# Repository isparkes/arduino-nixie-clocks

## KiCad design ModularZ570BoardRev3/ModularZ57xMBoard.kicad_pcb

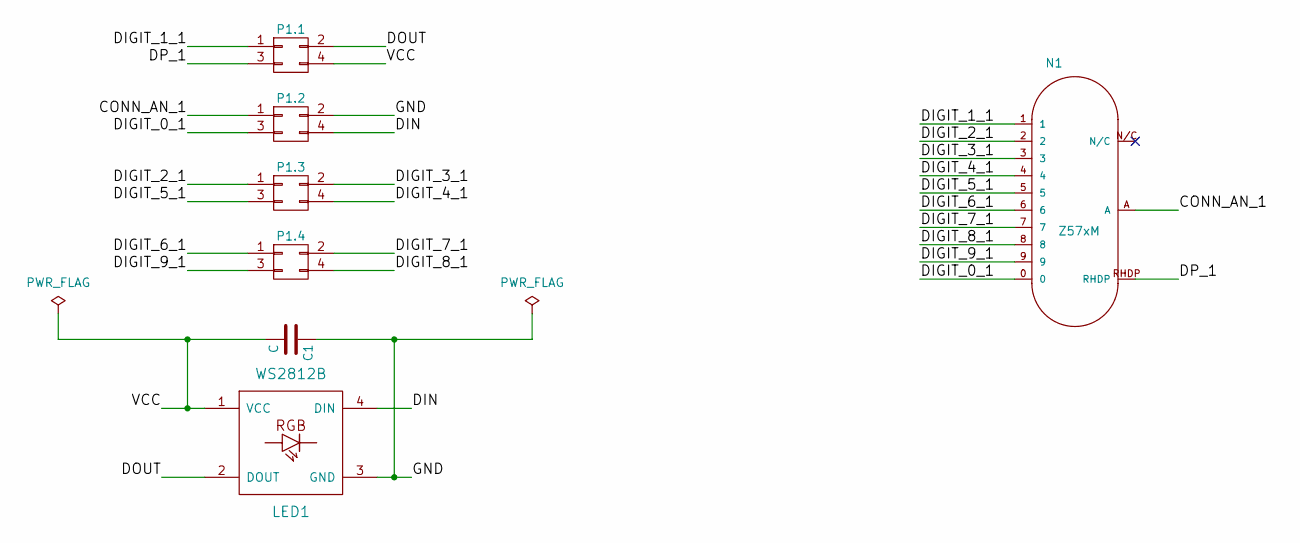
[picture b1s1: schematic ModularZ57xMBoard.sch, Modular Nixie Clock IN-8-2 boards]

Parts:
C1: C; C_1206_HandSoldering
LED1: WS2812B
N1: Z57xM; Z570M
P1.1, P1.2, P1.3, P1.4: CONN_02X02; Header_MA02-2

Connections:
/CONN_AN_1: N1.A, P1.2.1
/DIGIT_0_1: N1.0, P1.2.3
/DIGIT_1_1: N1.1, P1.1.1
/DIGIT_2_1: N1.2, P1.3.1
/DIGIT_3_1: N1.3, P1.3.2
/DIGIT_4_1: N1.4, P1.3.4
/DIGIT_5_1: N1.5, P1.3.3
/DIGIT_6_1: N1.6, P1.4.1
/DIGIT_7_1: N1.7, P1.4.2
/DIGIT_8_1: N1.8, P1.4.4
/DIGIT_9_1: N1.9, P1.4.3
/DIN: LED1.4 (DIN), P1.2.4
/DOUT: LED1.2 (DOUT), P1.1.2
/DP_1: N1.RHDP, P1.1.3
/GND: C1.1, LED1.3 (GND), P1.2.2
/VCC: C1.2, LED1.1 (VCC), P1.1.4

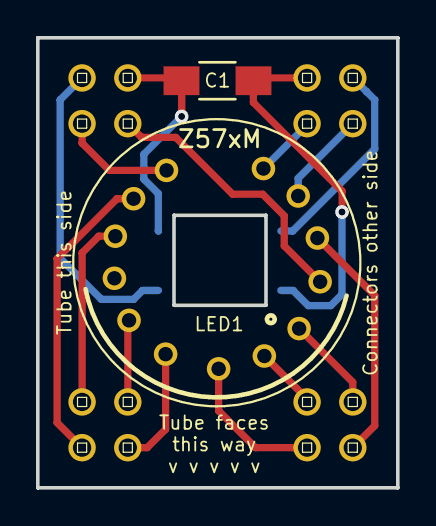
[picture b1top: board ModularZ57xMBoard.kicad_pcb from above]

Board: 2 copper layers, 20.0 x 25.0 mm, 7 parts (0 on the bottom side), 16 nets.

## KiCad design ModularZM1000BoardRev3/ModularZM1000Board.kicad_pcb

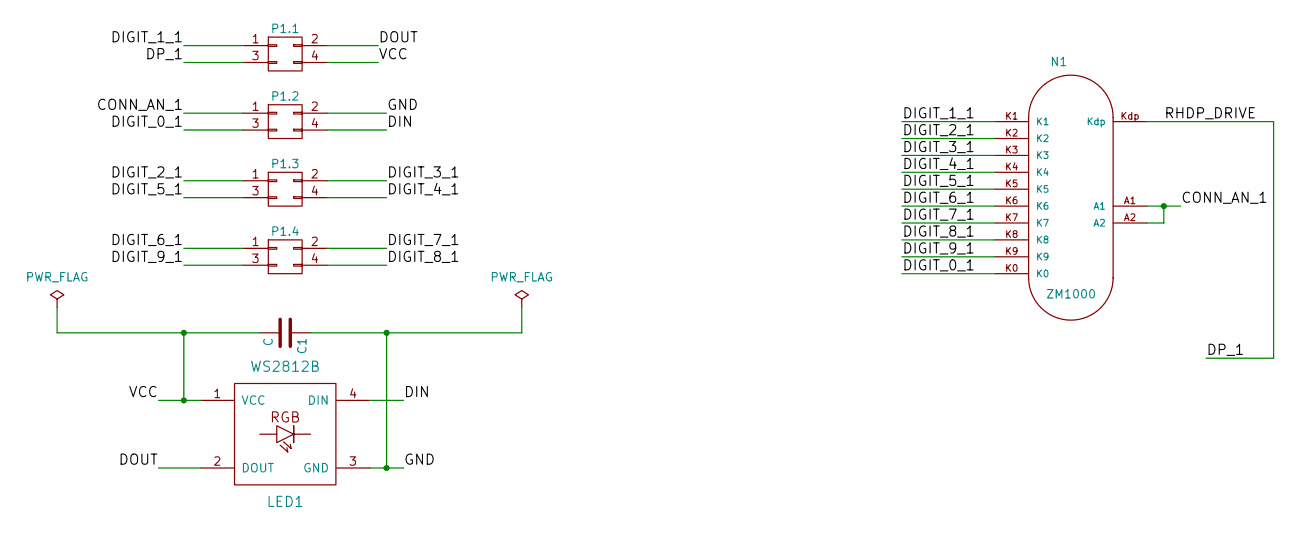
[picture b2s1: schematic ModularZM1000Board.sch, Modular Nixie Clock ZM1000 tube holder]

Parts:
C1: C; C_1206_HandSoldering
LED1: WS2812B
N1: ZM1000
P1.1, P1.2, P1.3, P1.4: CONN_02X02; Header_MA02-2

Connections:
/CONN_AN_1: N1.A1, N1.A2, P1.2.1
/DIGIT_0_1: N1.K0, P1.2.3
/DIGIT_1_1: N1.K1, P1.1.1
/DIGIT_2_1: N1.K2, P1.3.1
/DIGIT_3_1: N1.K3, P1.3.2
/DIGIT_4_1: N1.K4, P1.3.4
/DIGIT_5_1: N1.K5, P1.3.3
/DIGIT_6_1: N1.K6, P1.4.1
/DIGIT_7_1: N1.K7, P1.4.2
/DIGIT_8_1: N1.K8, P1.4.4
/DIGIT_9_1: N1.K9, P1.4.3
/DIN: LED1.4 (DIN), P1.2.4
/DOUT: LED1.2 (DOUT), P1.1.2
/DP_1: N1.Kdp, P1.1.3
/GND: C1.1, LED1.3 (GND), P1.2.2
/VCC: C1.2, LED1.1 (VCC), P1.1.4

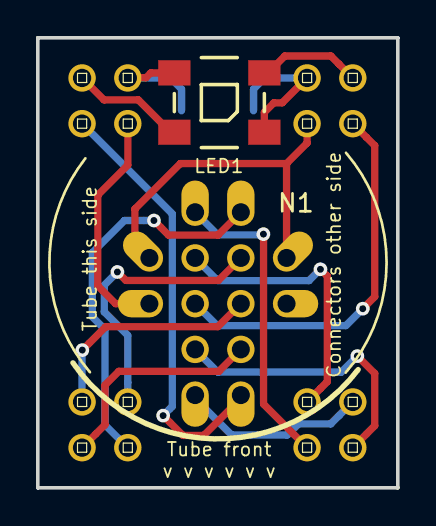
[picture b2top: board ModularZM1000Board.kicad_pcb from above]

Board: 2 copper layers, 20.0 x 25.0 mm, 7 parts (1 on the bottom side), 16 nets.

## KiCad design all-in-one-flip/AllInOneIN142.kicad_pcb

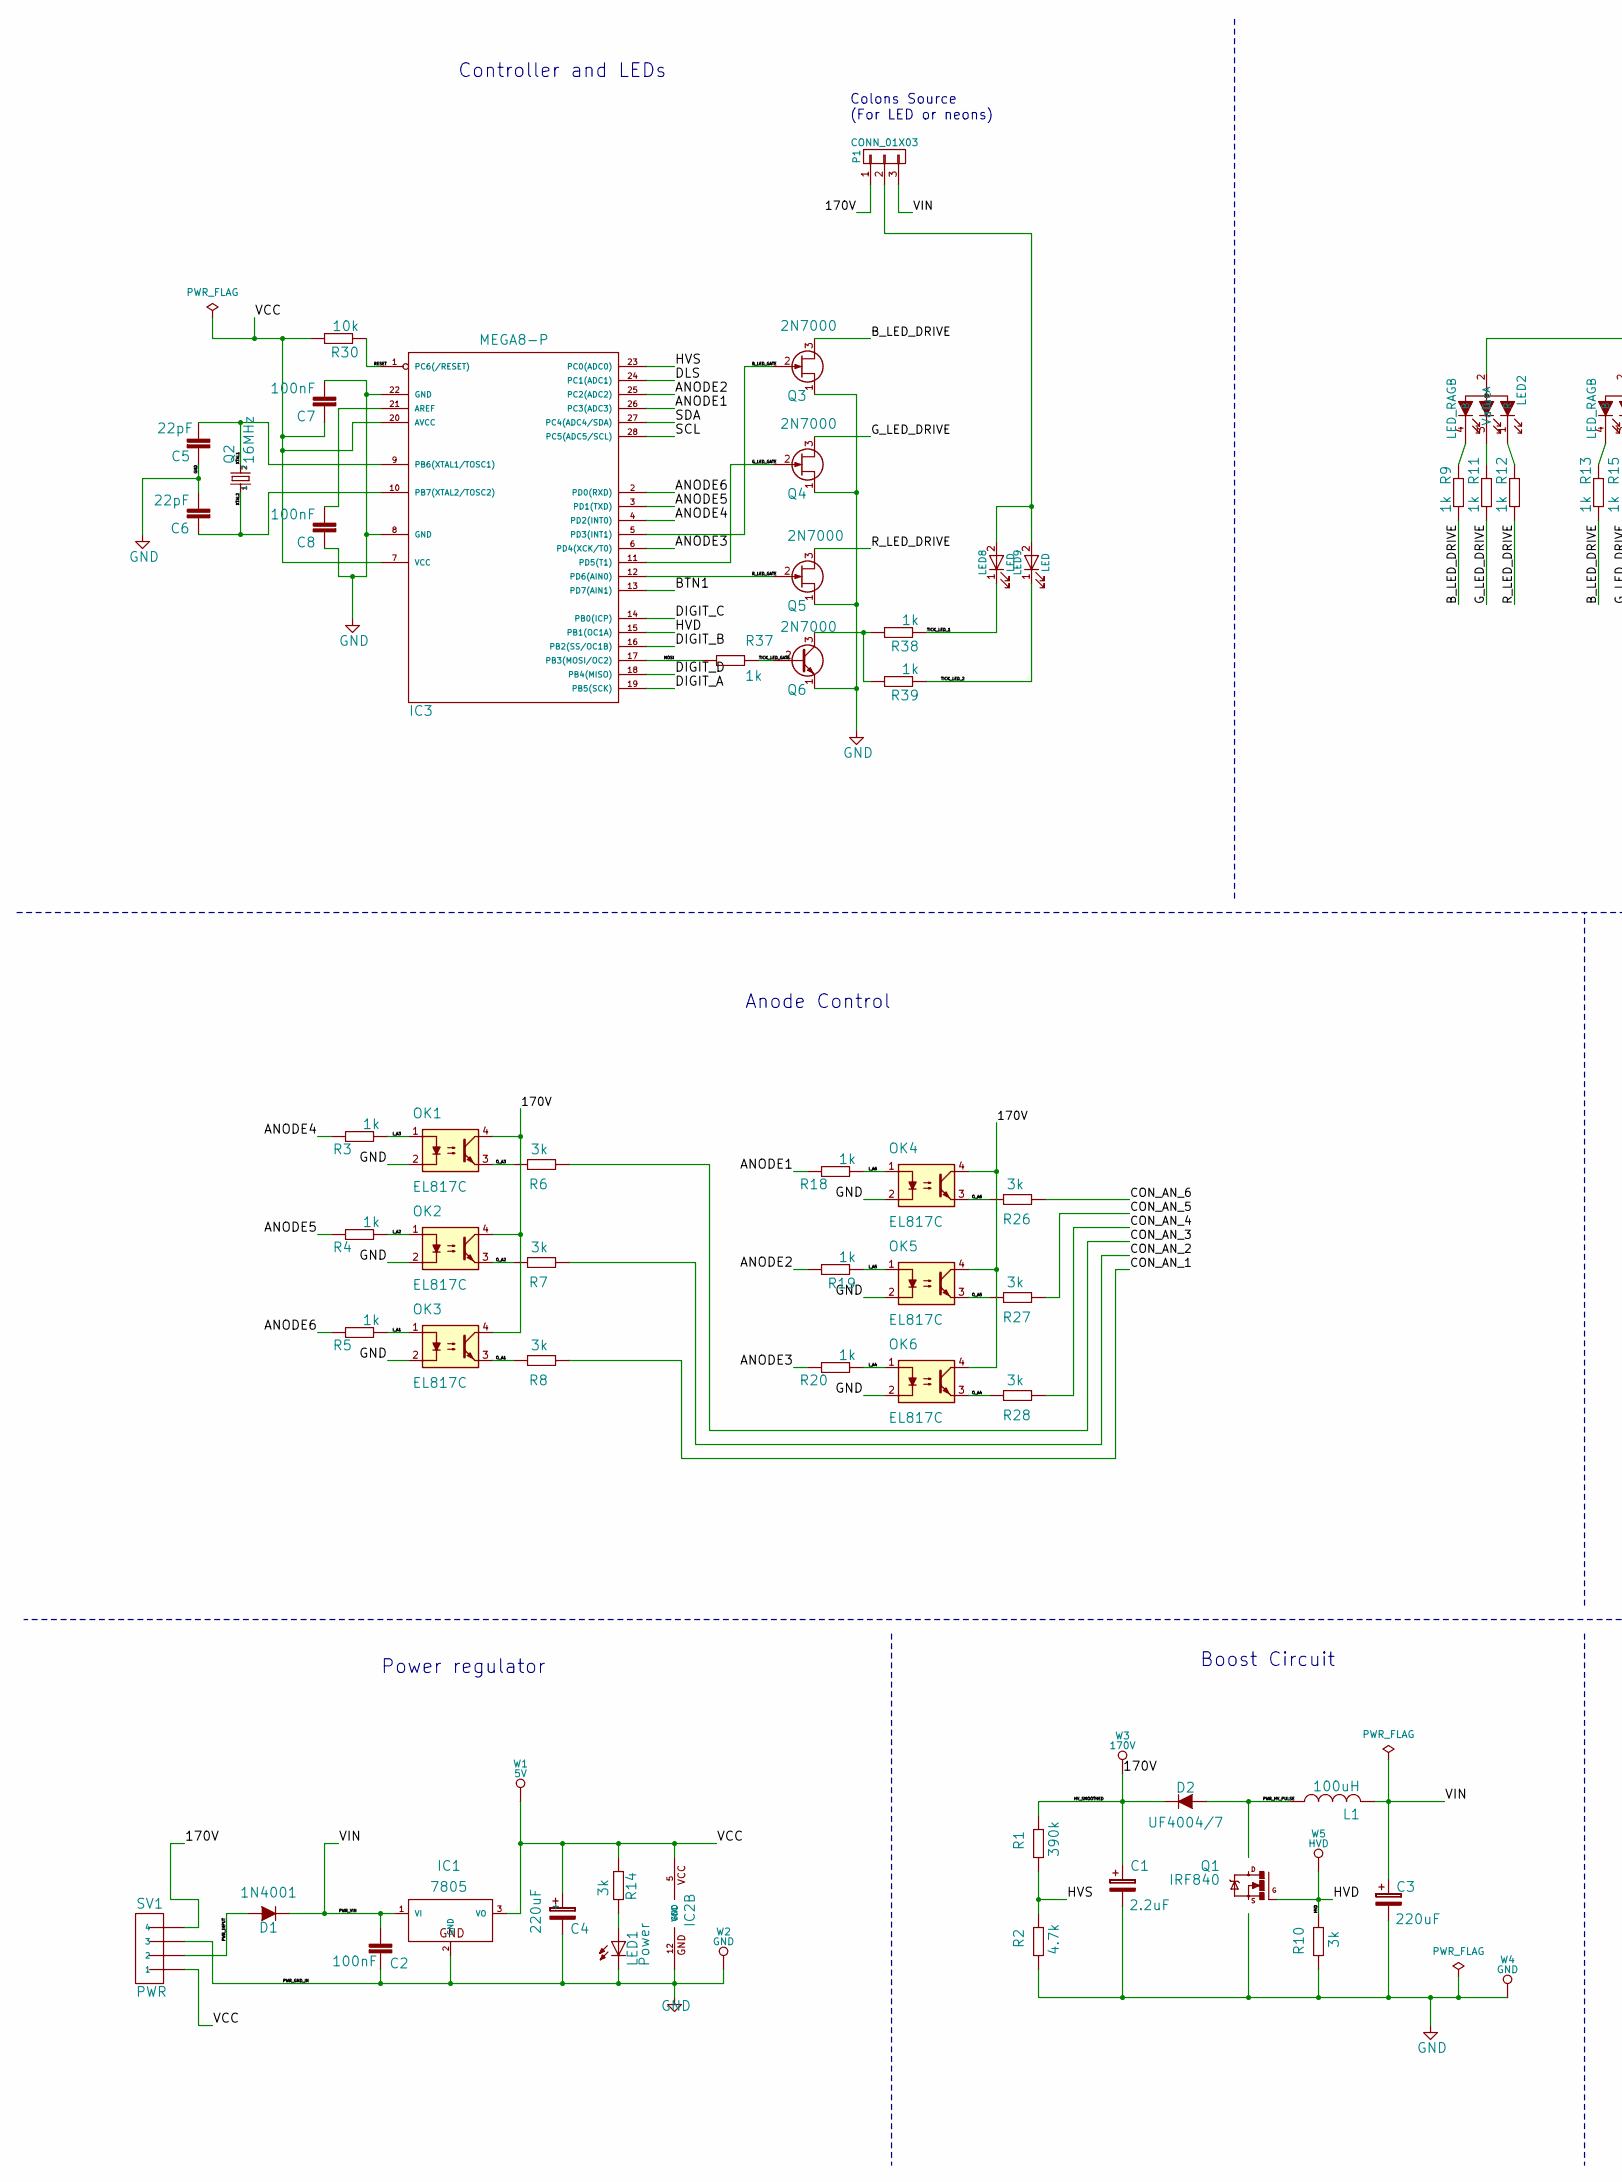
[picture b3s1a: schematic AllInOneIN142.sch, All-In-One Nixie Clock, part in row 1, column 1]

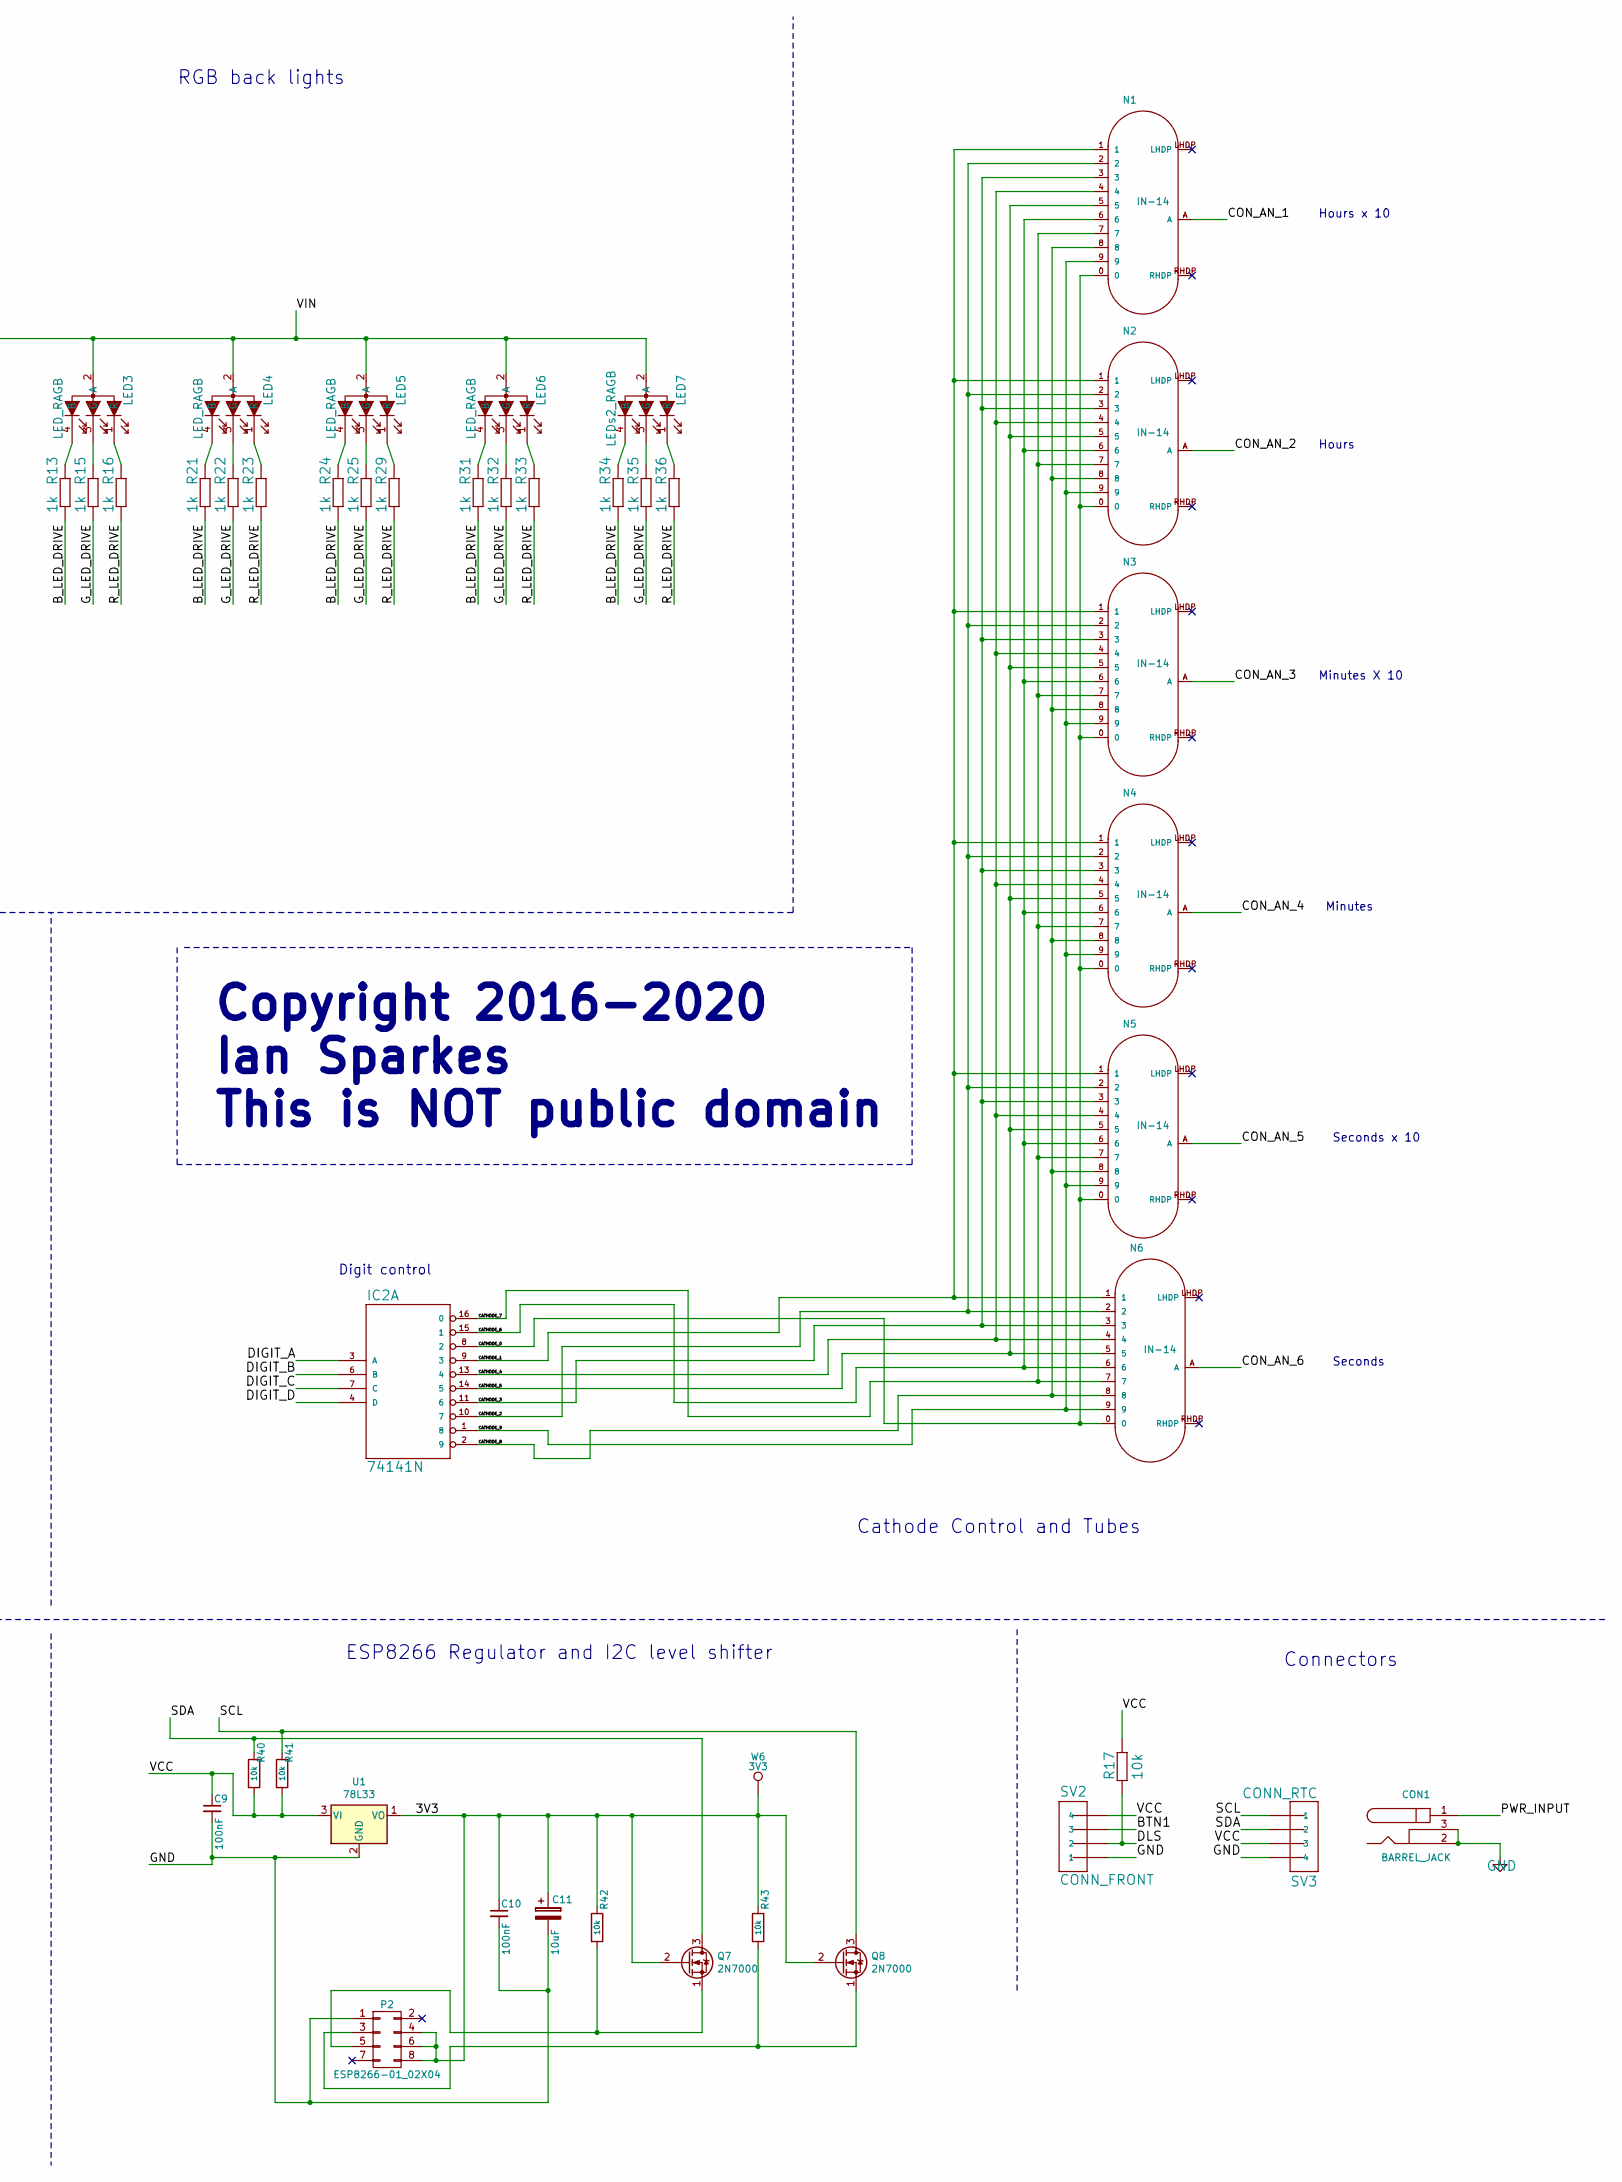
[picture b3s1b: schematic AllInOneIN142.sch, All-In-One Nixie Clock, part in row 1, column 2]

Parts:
C1: 2.2uF; C_Radial_D10_L11.2_P2.5_3.5
C2, C7, C8, C9, C10: 100nF; C025-024X044
C3, C4: 220uF; C_Radial_D6.3_L11.2_P2.5
C5, C6: 22pF; C025-024X044
C11: 10uF; C_Radial_D6.3_L11.2_P2.5
CON1: BARREL_JACK
D1: 1N4001; Diode_DO-41_1N4001
D2: UF4004/7; Diode_DO-41_1N4001
IC1: 7805; TRANSISTOR-POWER_TO220BV
IC2: 74141N; 74141_DIL16
IC3: MEGA8-P; 328P_DIL28
L1: 100uH; Inductor-100mH
LED1: Power; LED_3MM
LED2, LED3, LED4, LED5, LED6: LED_RAGB; LED5_RGB_CA_Offset
LED7: LEDs2_RAGB; LED5_RGB_CA_Offset
LED8, LED9: LED; LED-5MM-Centred
N1, N2, N3, N4, N5, N6: IN-14
OK1, OK2, OK3, OK4, OK5, OK6: EL817C; optocoupler-DIL04
P1: CONN_01X03; Header_MA03-1
P2: ESP8266-01_02X04; ESP8266_2x04
Q1: IRF840; 2N7000_TO92
Q2: 16MHz; Crystal_HC49-U_Vertical
Q3, Q4, Q5: 2N7000; TO-92_inline_2N7000
Q6: 2N7000; TO-92_inline_MPSA42
Q7, Q8: 2N7000; TO-92_2N7000_inline
R1: 390k; R-0207_2V
R2: 4.7k; R-0207_2V
R3, R4, R5, R9, R11, R12, R13, R15, R16, R18, R19, R20, R21, R22, R23, R24, R25, R29, R31, R32, R33, R34, R35, R36, R37, R38, R39: 1k; R-0207_2V
R6, R7, R8, R10, R14, R26, R27, R28: 3k; R-0207_2V
R17, R30, R40, R41, R42, R43: 10k; R-0207_2V
SV1: PWR; Header_MA04-1
SV2: CONN_FRONT; Header_MA04-1
SV3: CONN_RTC; Header_MA04-1
U1: 78L33; TO-92_2N7000_inline
W1: 5V; TESTPAD_P1-13
W2, W4: GND; TESTPAD_P1-13
W3: 170V; TESTPAD_P1-13
W5: HVD; TESTPAD_P1-13
W6: 3V3; TESTPAD_P1-13

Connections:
/3V3: C10.1, C11.1, P2.4 (CH_EN), P2.6 (RST), P2.8 (VCC), Q7.2 (G), Q8.2 (G), R42.1, R43.1, U1.1 (VO), W6.1
/170V: C1.1, D2.1 (K), OK1.4, OK2.4, OK3.4, OK4.4, OK5.4, OK6.4, P1.1, R1.2, SV1.4, W3.1
/ANODE1: IC3.26 (PC3(ADC3)), R18.2
/ANODE2: IC3.25 (PC2(ADC2)), R19.2
/ANODE3: IC3.6 (PD4(XCK/T0)), R20.2
/ANODE4: IC3.4 (PD2(INT0)), R3.2
/ANODE5: IC3.3 (PD1(TXD)), R4.2
/ANODE6: IC3.2 (PD0(RXD)), R5.2
/BTN1: IC3.13 (PD7(AIN1)), SV2.3
/B_LED_DRIVE: Q3.3 (D), R9.1, R13.1, R21.1, R24.1, R31.1, R34.1
/B_LED_GATE: IC3.5 (PD3(INT1)), Q3.2 (G)
/CATHODE_0: IC2.8 (2), N1.0, N2.0, N3.0, N4.0, N5.0, N6.0
/CATHODE_1: IC2.9 (3), N1.1, N2.1, N3.1, N4.1, N5.1, N6.1
/CATHODE_2: IC2.10 (7), N1.2, N2.2, N3.2, N4.2, N5.2, N6.2
/CATHODE_3: IC2.11 (6), N1.3, N2.3, N3.3, N4.3, N5.3, N6.3
/CATHODE_4: IC2.13 (4), N1.4, N2.4, N3.4, N4.4, N5.4, N6.4
/CATHODE_5: IC2.14 (5), N1.5, N2.5, N3.5, N4.5, N5.5, N6.5
/CATHODE_6: IC2.15 (1), N1.6, N2.6, N3.6, N4.6, N5.6, N6.6
/CATHODE_7: IC2.16 (0), N1.7, N2.7, N3.7, N4.7, N5.7, N6.7
/CATHODE_8: IC2.2 (9), N1.8, N2.8, N3.8, N4.8, N5.8, N6.8
/CATHODE_9: IC2.1 (8), N1.9, N2.9, N3.9, N4.9, N5.9, N6.9
/CON_AN_1: N1.A, R8.1
/CON_AN_2: N2.A, R7.1
/CON_AN_3: N3.A, R6.1
/CON_AN_4: N4.A, R28.1
/CON_AN_5: N5.A, R27.1
/CON_AN_6: N6.A, R26.1
/DIGIT_A: IC2.3 (A), IC3.19 (PB5(SCK))
/DIGIT_B: IC2.6 (B), IC3.16 (PB2(SS/OC1B))
/DIGIT_C: IC2.7 (C), IC3.14 (PB0(ICP))
/DIGIT_D: IC2.4 (D), IC3.18 (PB4(MISO))
/DLS: IC3.24 (PC1(ADC1)), R17.1, SV2.2
/G_LED_DRIVE: Q4.3 (D), R11.1, R15.1, R22.1, R25.1, R32.1, R35.1
/G_LED_GATE: IC3.11 (PD5(T1)), Q4.2 (G)
/HVD: IC3.15 (PB1(OC1A)), Q1.1, Q1.G, R10.2, W5.1
/HVS: IC3.23 (PC0(ADC0)), R1.1, R2.2
/I_A1: OK3.1, R5.1
/I_A2: OK2.1, R4.1
/I_A3: OK1.1, R3.1
/I_A4: OK6.1, R20.1
/I_A5: OK5.1, R19.1
/I_A6: OK4.1, R18.1
/MOSI: IC3.17 (PB3(MOSI/OC2)), R37.1
/O_A1: OK3.3, R8.2
/O_A2: OK2.3, R7.2
/O_A3: OK1.3, R6.2
/O_A4: OK6.3, R28.2
/O_A5: OK5.3, R27.2
/O_A6: OK4.3, R26.2
/PWR_HV_PULSE: D2.2 (A), L1.1, Q1.2, Q1.D
/PWR_INPUT: CON1.1, D1.2 (A), SV1.2
/PWR_VIN: C2.2, C3.1, D1.1 (K), IC1.1 (VI), L1.2, LED2.2 (A), LED3.2 (A), LED4.2 (A), LED5.2 (A), LED6.2 (A), LED7.2 (A), P1.3
/RESET: IC3.1 (PC6(/RESET)), R30.1
/R_LED_DRIVE: Q5.3 (D), R12.1, R16.1, R23.1, R29.1, R33.1, R36.1
/R_LED_GATE: IC3.12 (PD6(AIN0)), Q5.2 (G)
/SCL: IC3.28 (PC5(ADC5/SCL)), Q8.3 (D), R41.1, SV3.1
/SDA: IC3.27 (PC4(ADC4/SDA)), Q7.3 (D), R40.1, SV3.2
/TICK_LED_1: LED8.1 (K), R38.1
/TICK_LED_2: LED9.1 (K), R39.1
/TICK_LED_GATE: Q6.2 (B), R37.2
/VCC: C4.1, C7.1, C9.1, IC1.3 (VO), IC2.5 (VCC), IC3.7 (VCC), IC3.20 (AVCC), R14.1, R17.2, R30.2, R40.2, R41.2, SV1.1, SV2.4, SV3.3, U1.3 (VI), W1.1
/XTAL1: C5.2, IC3.9 (PB6(XTAL1/TOSC1)), Q2.2
/XTAL2: C6.1, IC3.10 (PB7(XTAL2/TOSC2)), Q2.1
GND: C1.2, C2.1, C3.2, C4.2, C5.1, C6.2, C7.2, C8.1, C9.2, C10.2, C11.2, CON1.2, CON1.3, IC1.2 (GND), IC2.12 (GND), IC3.8 (GND), IC3.22 (GND), LED1.K (C), OK1.2, OK2.2, OK3.2, OK4.2, OK5.2, OK6.2, P2.1 (GND), Q1.3, Q1.S, Q3.1 (S), Q4.1 (S), Q5.1 (S), Q6.1 (E), R2.1, R10.1, SV1.3, SV2.1, SV3.4, U1.2 (GND), W2.1, W4.1; also elsewhere on the board
unnamed: C8.2, IC3.21 (AREF)
unnamed: LED1.A, R14.2
unnamed: LED2.1 (R), R12.2
unnamed: LED2.3 (G), R11.2
unnamed: LED2.4 (B), R9.2
unnamed: LED3.1 (R), R16.2
unnamed: LED3.3 (G), R15.2
unnamed: LED3.4 (B), R13.2
unnamed: LED4.1 (R), R23.2
unnamed: LED4.3 (G), R22.2
unnamed: LED4.4 (B), R21.2
unnamed: LED5.1 (R), R29.2
unnamed: LED5.3 (G), R25.2
unnamed: LED5.4 (B), R24.2
unnamed: LED6.1 (R), R33.2
unnamed: LED6.3 (G), R32.2
unnamed: LED6.4 (B), R31.2
unnamed: LED7.1 (R), R36.2
unnamed: LED7.3 (G), R35.2
unnamed: LED7.4 (B), R34.2
unnamed: LED8.2 (A), LED9.2 (A), P1.2
unnamed: P2.3 (GPIO2), Q8.1 (S), R43.2
unnamed: P2.5 (GPIO0), Q7.1 (S), R42.2
unnamed: Q6.3 (C), R38.2, R39.2

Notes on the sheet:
Boost Circuit
Anode Control
Power regulator
Digit control
Connectors
Seconds
Seconds x 10
Minutes
Minutes X 10
Hours
Hours x 10
Colons Source (For LED or neons)
ESP8266 Regulator and I2C level shifter
Copyright 2016-2020 Ian Sparkes This is NOT public domain
Cathode Control and Tubes
RGB back lights
Controller and LEDs

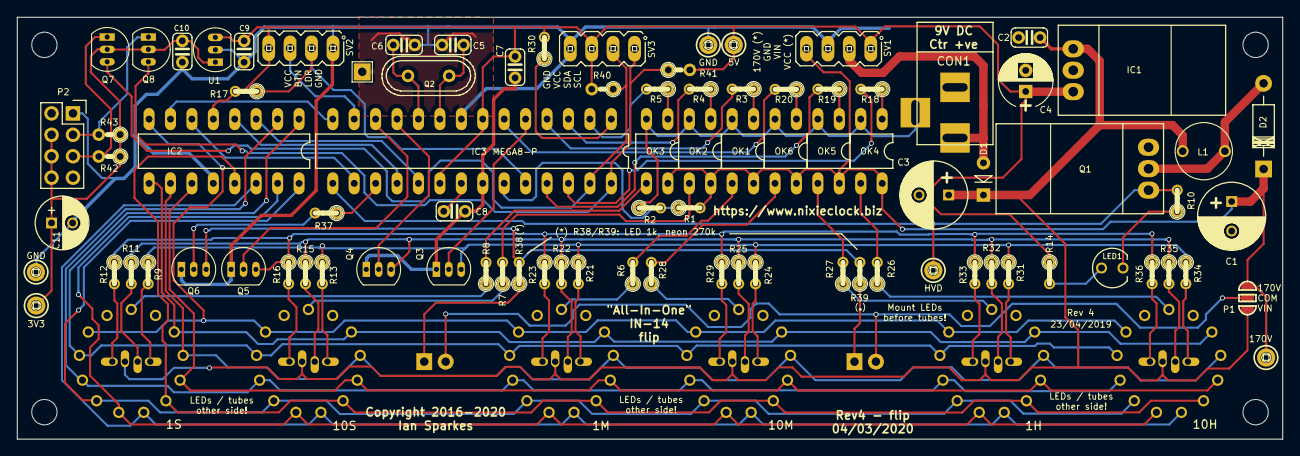
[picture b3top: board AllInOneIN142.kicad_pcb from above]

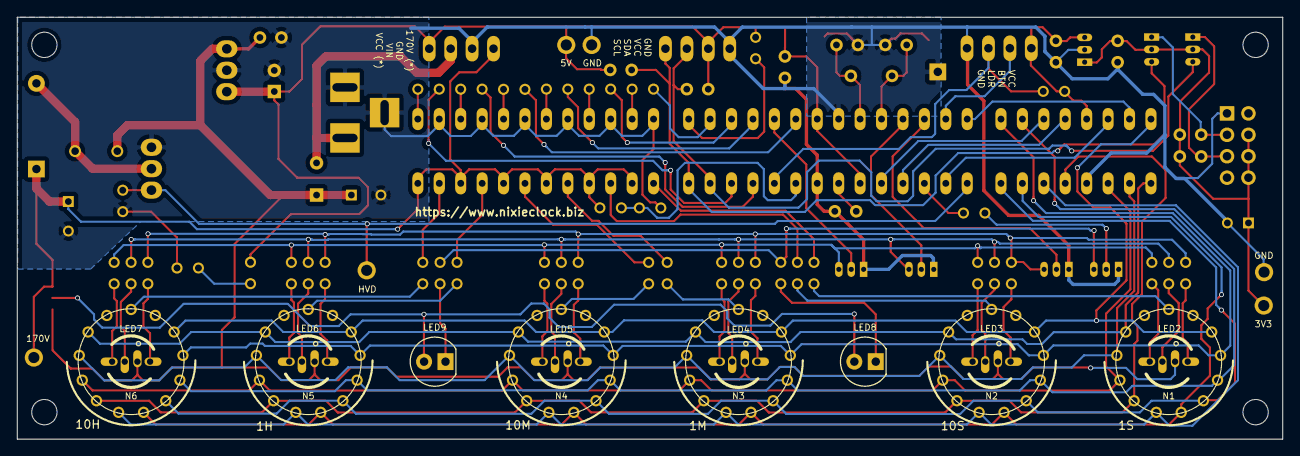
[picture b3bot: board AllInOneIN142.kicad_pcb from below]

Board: 2 copper layers, 150.0 x 50.0 mm, 107 parts (14 on the bottom side), 88 nets.

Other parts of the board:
GND Can: TestPoint_THTPad_2.0x2.0mm_Drill1.0mm
MH1, MH2, MH3, MH4: MountingHole_3mm

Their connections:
GND: GND Can.1; also elsewhere on the board

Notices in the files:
all-in-one-flip/AllInOneIN142.sch:
Copyright 2016-2019
